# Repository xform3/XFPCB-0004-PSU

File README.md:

# XFPCB-0004 Regulated Bipolar Dual Voltage AC to ±DC Power Supply  
Dual ±DC Output Power Supply, built around LM79XX & LM18XX regulators. This power supply is intended to be used with VAC center tapped transformer for audio/amplifier applications.

## Specifications 
(±18VDC Example)
- Input Voltage:  18-0-18 VAC 1A @ 47-63Hz
- Output Voltage: +18 VDC | 0 VDC | -18 VDC
- Throught-hole components, single-layer clad.

## Features
- Input Voltage Filtering
- Low Output Ripple, Voltage Stable to ±0.005VDC

## Variations 
(By replacing LM78xx & LM79xx Voltage can be adjusted respectively)
* 6V-0-6V (12W)   - LM7906 & LM7806
* 12V-0-12V (24W) - LM7912 & LM7812
* 15V-0-15V (30W) - LM7915 & LM7816
* 18V-0-18V (36W) - LM7918 & LM7818

## [Compatible with XFPCB-0003_AMP Class-AB Amplifier](https://github.com/xform3/xfpcb-0003-amp)

## Included Files:
* [xf3_psu](https://github.com/xform3/XFPCB-0004-PSU/tree/master/xf3_psu)  - *KiCAD Project Files*
* [xf3_psu_mask](https://github.com/xform3/XFPCB-0004-PSU/tree/master/xf3_psu_mask) - *PCB Gerber, Drill, Silk/Solder Masks, Positive and Negative plots*
* [xf3-KiCad-Library](https://github.com/xform3/xf3-KiCad-Library)  - *KiCAD Library Files; footprints, .step and .wrl component models, schema lib.*

## Application:
(±18VDC Example)

## Schematic
(±18VDC Example)

## PCB
(±18VDC Example)

## PROTOTYPE

## KiCad 3D

## FreeCAD Model

## VCT Center tap Transformer

## Amplifier [Using: XFPCB-0003 Class-AB Amplifier 20-30W LM1875 or TDA2030](https://github.com/xform3/xfpcb-0003-amp)

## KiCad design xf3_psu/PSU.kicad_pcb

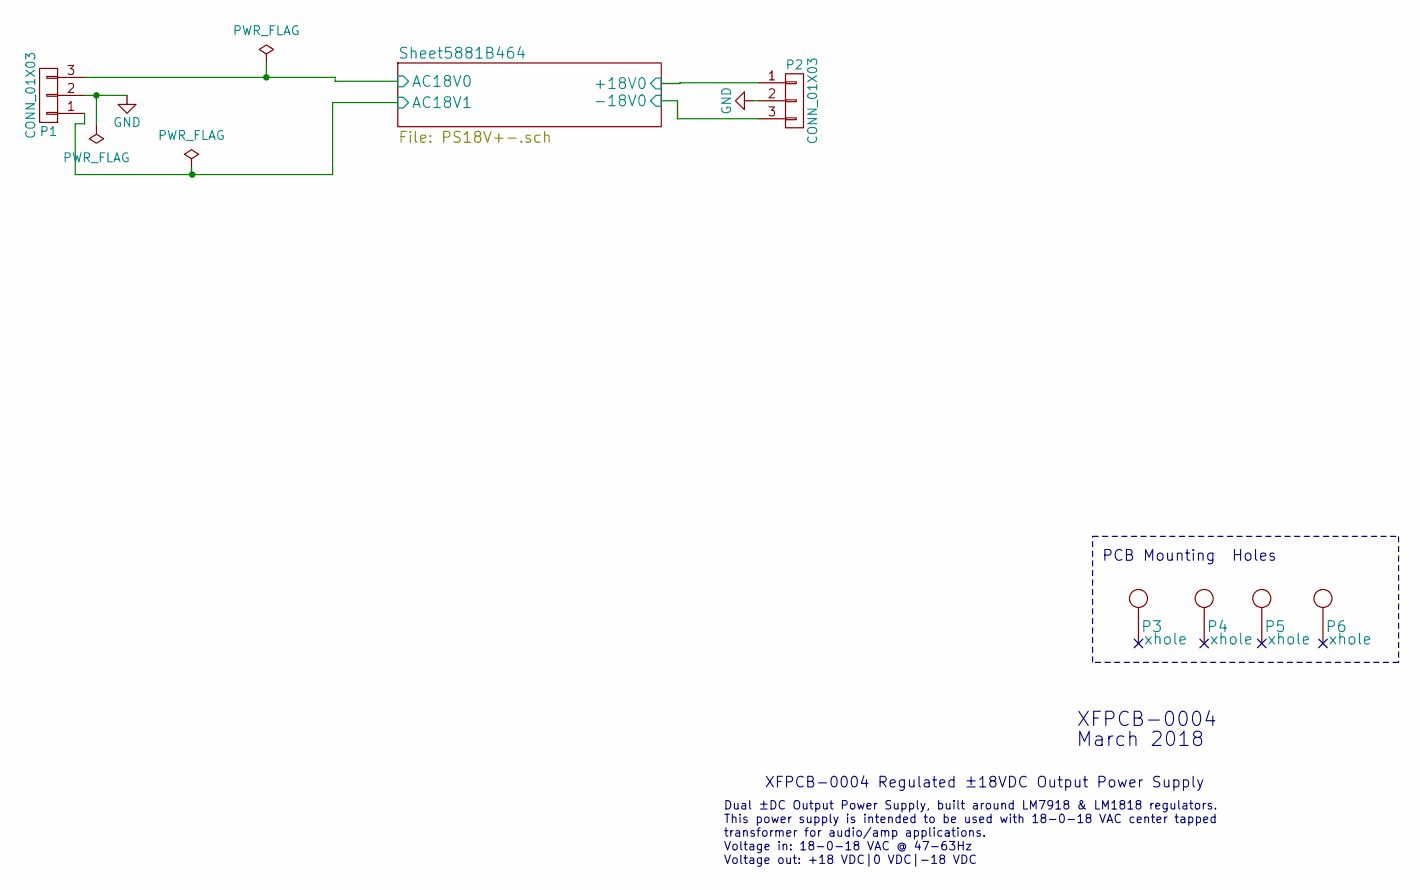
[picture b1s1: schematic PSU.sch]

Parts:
P1: CONN_01X03; x_PhoenixX3flipped
P2: CONN_01X03; x_PhoenixX3
P3, P4, P5, P6: xhole; x_HoleRound

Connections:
/Sheet5881B464/+18V0: P2.1; also elsewhere on the board
/Sheet5881B464/-18V0: P2.3; also elsewhere on the board
/Sheet5881B464/AC18V0: P1.3; also elsewhere on the board
/Sheet5881B464/AC18V1: P1.1; also elsewhere on the board
GND: P1.2, P2.2; also elsewhere on the board

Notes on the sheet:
Dual ±DC Output Power Supply, built around LM7918 & LM1818 regulators. This power supply is intended to be used with 18-0-18 VAC center tapped transformer for audio/amp applications. Voltage in: 18-0-18 VAC @ 47-63Hz Voltage out: +18 VDC|0 VDC|-18 VDC
XFPCB-0004 Regulated ±18VDC Output Power Supply
XFPCB-0004
March 2018
PCB Mounting Holes

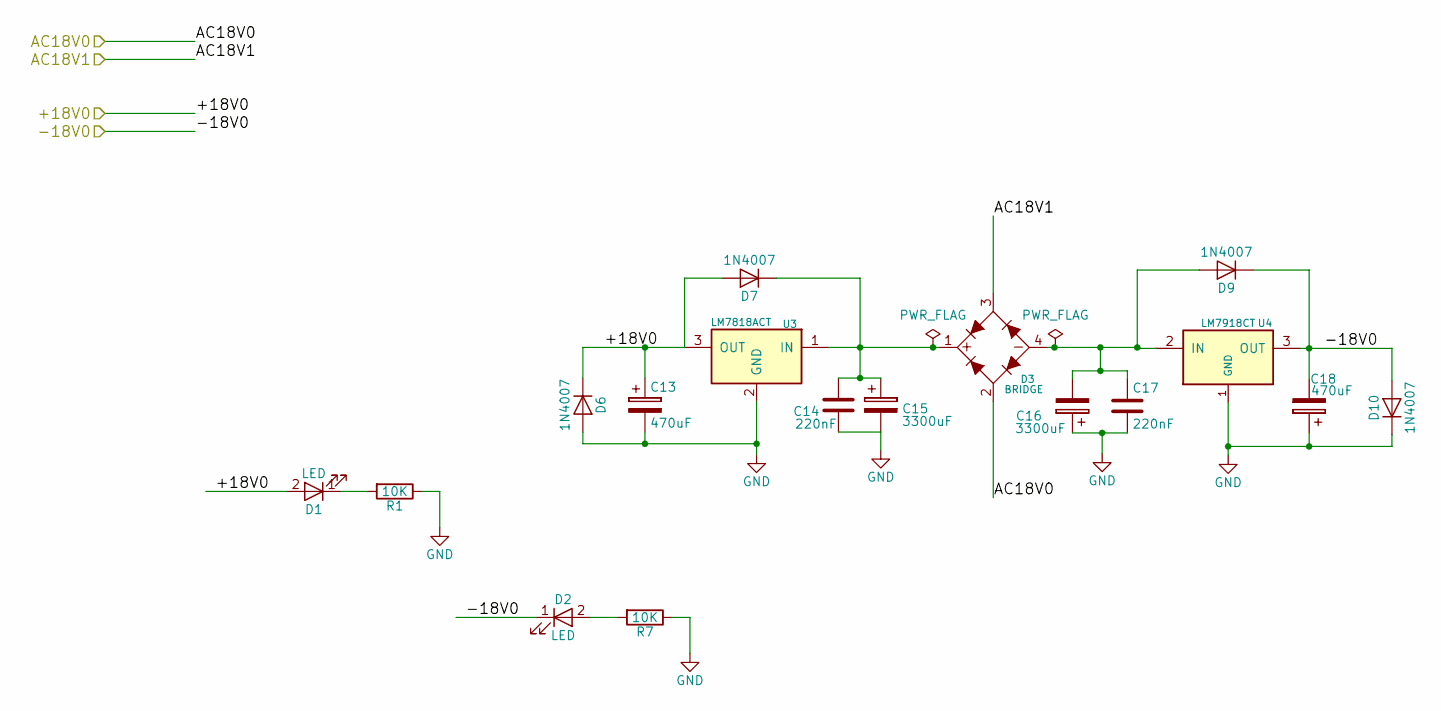
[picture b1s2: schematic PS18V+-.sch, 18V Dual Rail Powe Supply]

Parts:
C13, C18: 470uF; x_CapRadial10mm
C14, C17: 220nF; x_CapDisk9mm
C15, C16: 3300uF; x_CapRadial13mm
D1: LED; x_Led
D2: LED; x_LedBlue
D3: BRIDGE; x_DiodeBridge
D6, D7, D9, D10: 1N4007; x_Diode
R1, R7: 10K; x_ResistorHorizontalRM10mm
U3: LM7818ACT; x_TO220Heatsink
U4: LM7918CT; x_TO220Heatsink

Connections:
/Sheet5881B464/+18V0: C13.1, D1.2 (A), D6.1 (K), D7.2 (A), U3.3 (OUT); also elsewhere on the board
/Sheet5881B464/-18V0: C18.2, D2.1 (K), D9.1 (K), D10.2 (A), U4.3 (OUT); also elsewhere on the board
/Sheet5881B464/AC18V0: D3.2 (~1); also elsewhere on the board
/Sheet5881B464/AC18V1: D3.3 (~2); also elsewhere on the board
GND: C13.2, C14.2, C15.2, C16.1, C17.2, C18.1, D6.2 (A), D10.1 (K), R1.1, R7.1, U3.2 (GND), U4.1 (GND); also elsewhere on the board
unnamed: C14.1, C15.1, D3.1 (V+), D7.1 (K), U3.1 (IN)
unnamed: C16.2, C17.1, D3.4 (V-), D9.2 (A), U4.2 (IN)
unnamed: D1.1 (K), R1.2
unnamed: D2.2 (A), R7.2

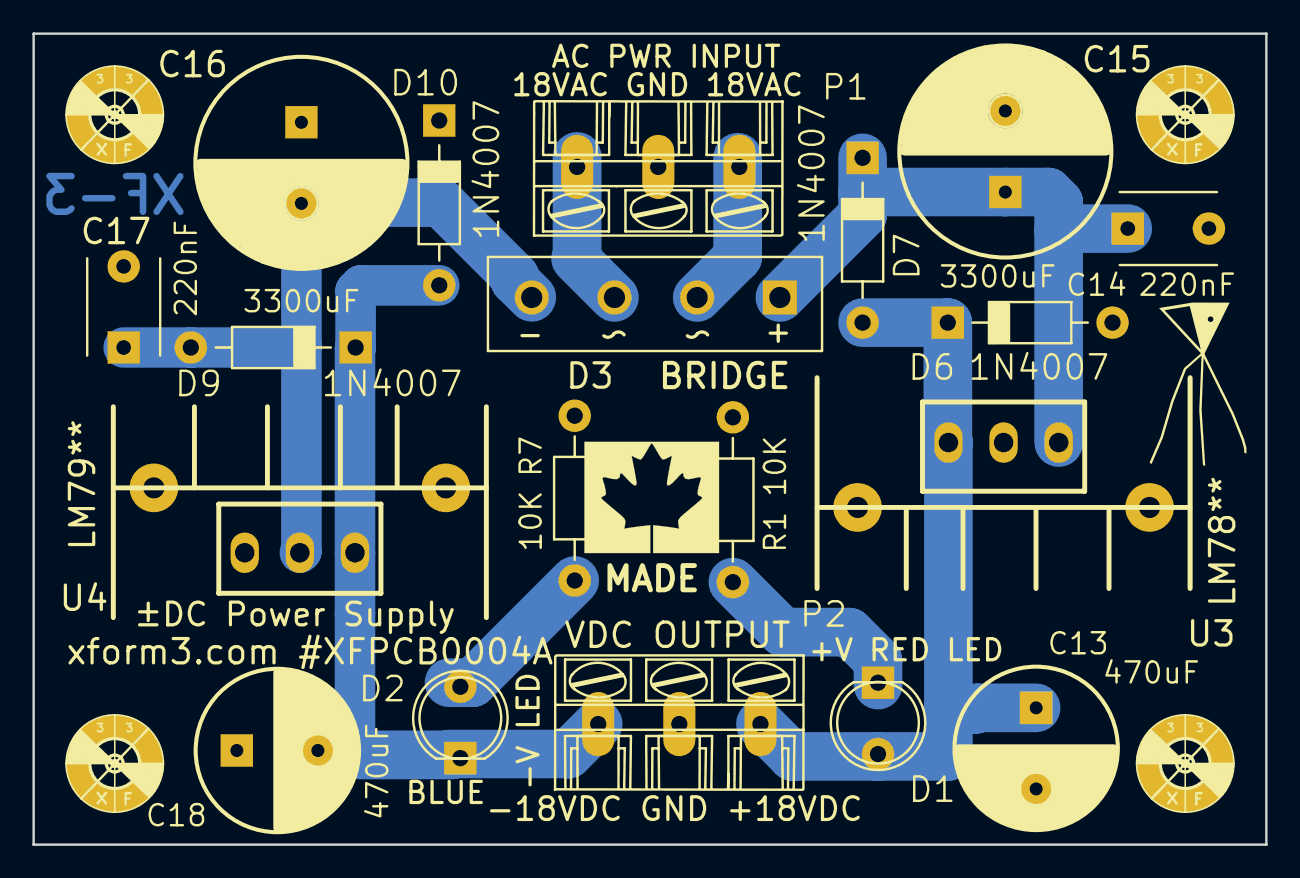
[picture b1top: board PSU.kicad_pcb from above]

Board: 2 copper layers, 76.0 x 50.0 mm, 24 parts (0 on the bottom side), 9 nets.

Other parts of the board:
svg2mod: G***; x_gx_xform_5x8_Silk

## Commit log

2018-03-20 Set theme jekyll-theme-slate
2018-03-20 Name corrections
2018-03-20 new graphics
2018-03-20 Set theme jekyll-theme-minimal
2018-06-01 adds photos, silkscreen changes
2018-06-02 adds photos
2018-06-03 silkscreen edits
2018-06-03 silkscreen changes
2018-06-07 fixed silk, changed graphics
